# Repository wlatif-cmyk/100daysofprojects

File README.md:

100 Days of Projects — TikTok Series 

https://www.tiktok.com/@yappingaddiction

https://www.instagram.com/yappingaddiction/

Welcome to my 100-day challenge!  

Every day, I build something small, fun, or weird — and post it on TikTok.  

This repo collects the code, notes, and mini-projects from each day.

Follow along as this slowly turns into a chaotic but glorious archive of experiments. 

---

📆 Daily Projects

Day 1 — Traffic light system

Day 2 — Light meter that runs off of ultrasonic sensor

Day 3 — Ball game with LCD Module

Day 4 — Fan Motion Detection 

Day 5 — LED colour changer

Day 6 — Anti-procrastination tool

Day 7 — Anti-procrastination tool major improvements - added timer, timer reset button, and improved screen contrasting

Day 8 — LED Night light

Day 9 — Button piano

Day 10 — Improvements to LED night light - added alarm system

Day 11 — Clothing temperature/humidity sensor

Day 12 — Arduino project generator

Day 13 — Servo motor joystick control

Day 14 — Servo motor joystick control + Remote control using IR sensors

Day 15 — Budgeting dashboard site 

Day 16 — Servo motor hand recognition control

Day 17 — Servo motor hand recognition control2 - same concept but motor moves when hand open/closes

Day 18 — Interview prep tool to prioritize/learn proper eye contact 

Day 19 — Funny face tool using OpenCV

Day 20 — Advanced touchless volume controller

Day 21 — Motion gesture controlled brightness

Day 22 — Motion gesture cursor 

Day 23 — Spotify playlist analyzer

Day 24 — Currency converter 

Day 25 — Weather app

Day 26 — To do list app

Day 27 — "Panda" - designer player upon detection of panda plushie 

Day 28 — Basic chatbot

Day 29 — Number guesser

Day 30 — Motion gesture controlled LED 

Day 31 — RFID card reader 

Day 32 — Password manager 

Day 33 — Expense Tracker

Day 34 — Soldered project (no code)

Day 35 — Cheat code controlled door lock 

Day 36 — Added pin unlock on phone for door lock 

Day 37 — Built final prototype for door lock 

Day 38 — Portable system wiring (No code)

Day 39 — Joystick controlled cursor

Day 40 — Hypnotic art drawing game on python

Day 41 — Esp32 portable communication led project 

Day 42 — Mood bot

Day 43 — Mini Spotify display 

Day 44 — Added buttons to Spotify display 

Day 45 — Math alarm clock 

Day 46 — Improved math alarm clock

Day 47 — STM32 power modes 

Day 48 — Pong on joysticks

Day 49 — ESP32 WIFI network ranking

Day 50 — Balloon popper 

Day 51 — Productivity measure using CV 

Day 52 — ESP32 WIFI channel interference detector 

Day 53 — Improved day 18 project (interview eye contact detector) to give score afterward

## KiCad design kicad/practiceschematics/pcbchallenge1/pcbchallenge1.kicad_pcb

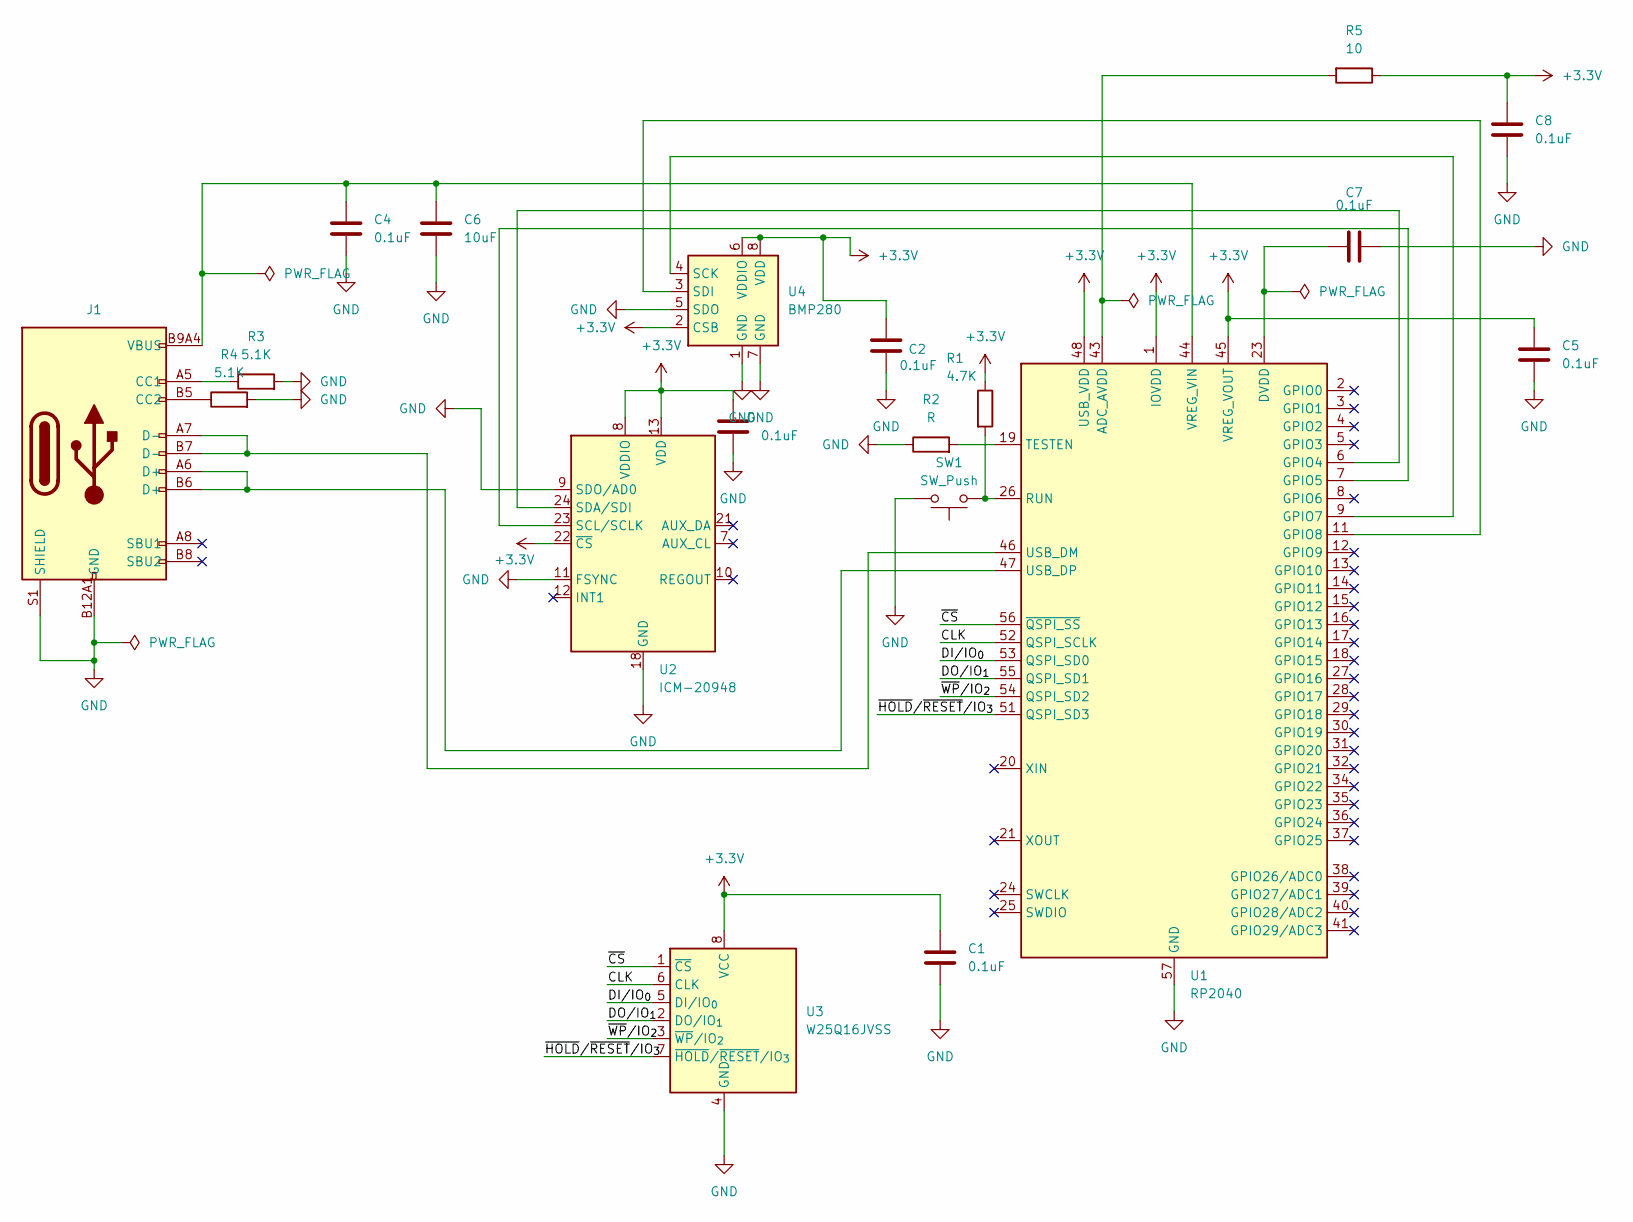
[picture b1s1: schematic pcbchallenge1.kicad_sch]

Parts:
C1, C2, C3, C4, C5, C7, C8: 0.1uF; CP_Elec_3x5.3
C6: 10uF; CP_Elec_4x5.8
J1: Connector, USB-TYPE-C-16P; TYPE-C-SMD_HX-TYPE-C-16PIN; LCSC C2927039
R1: 4.7K; R_0201_0603Metric
R2: R; R_0201_0603Metric
R3, R4: 5.1K; R_0201_0603Metric
R5: 10; R_0201_0603Metric
SW1: SW_Push; R_0201_0603Metric
U1: RP2040; QFN-56-1EP_7x7mm_P0.4mm_EP3.2x3.2mm
U2: ICM-20948; InvenSense_QFN-24_3x3mm_P0.4mm
U3: W25Q16JVSS; SOIC-8_5.3x5.3mm_P1.27mm
U4: BMP280; Bosch_LGA-8_2x2.5mm_P0.65mm_ClockwisePinNumbering

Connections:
+3.3V: C1.1, C2.1, C3.1, C5.1, C8.1, R1.1, R5.1, U1.1 (IOVDD), U1.10 (IOVDD), U1.22 (IOVDD), U1.33 (IOVDD), U1.42 (IOVDD), U1.45 (VREG_VOUT), U1.48 (USB_VDD), U1.49 (IOVDD), U2.8 (VDDIO), U2.13 (VDD), U2.22 (~CS), U3.8 (VCC), U4.2 (CSB), U4.6 (VDDIO), U4.8 (VDD)
GND: C1.2, C2.2, C3.2, C4.2, C5.2, C6.2, C7.2, C8.2, J1.A12B1 (GND), J1.B12A1 (GND), J1.S1 (SHIELD), R2.1, R3.2, R4.2, SW1.2, U1.57 (GND), U2.9 (SDO/AD0), U2.11 (FSYNC), U2.18 (GND), U2.20 (GND), U3.4 (GND), U4.1 (GND), U4.5 (SDO), U4.7 (GND)
unnamed: C7.1, U1.23 (DVDD), U1.50 (DVDD)
unnamed: J1.A5 (CC1), R3.1
unnamed: J1.B5 (CC2), R4.1
unnamed: R5.2, U1.43 (ADC_AVDD)
unnamed: U1.6 (GPIO4), U2.24 (SDA/SDI)
unnamed: U1.7 (GPIO5), U2.23 (SCL/SCLK)
unnamed: U1.9 (GPIO7), U4.4 (SCK)
unnamed: U1.11 (GPIO8), U4.3 (SDI)
unnamed: U1.52 (QSPI_SCLK), U3.6 (CLK)
unnamed: U1.53 (QSPI_SD0), U3.5 (DI/IO_{0})
unnamed: U1.55 (QSPI_SD1), U3.2 (DO/IO_{1})
unnamed: U1.54 (QSPI_SD2), U3.3 (~WP/IO_{2})
unnamed: U1.51 (QSPI_SD3), U3.7 (~HOLD/~RESET/IO_{3})
unnamed: R1.2, SW1.1, U1.26 (RUN)
unnamed: R2.2, U1.19 (TESTEN)
unnamed: J1.A7 (D-), J1.B7 (D-), U1.46 (USB_DM)
unnamed: J1.A6 (D+), J1.B6 (D+), U1.47 (USB_DP)
unnamed: C4.1, C6.1, J1.A9B4 (VBUS), J1.B9A4 (VBUS), U1.44 (VREG_VIN)
unnamed: U1.56 (~QSPI_SS), U3.1 (~CS)

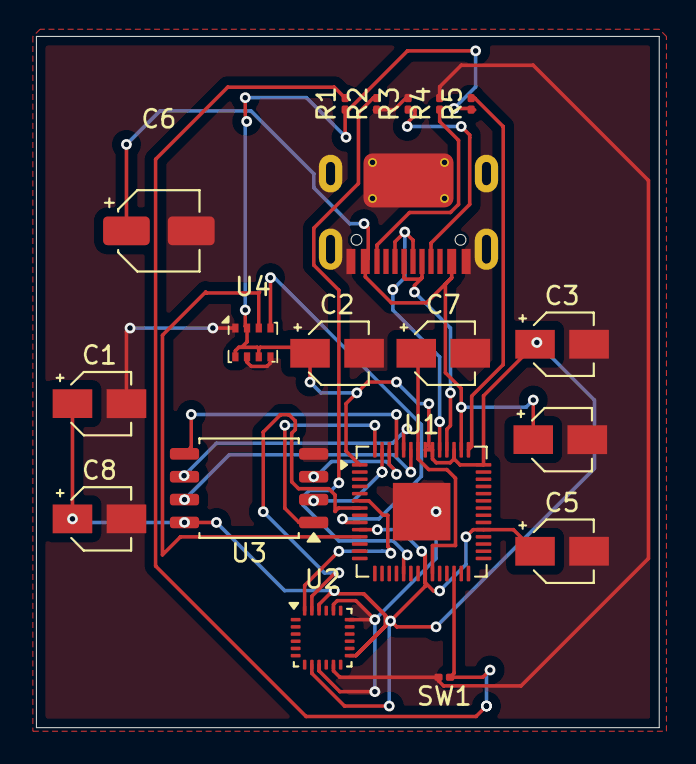
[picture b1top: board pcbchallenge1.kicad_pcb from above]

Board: 2 copper layers, 34.6 x 38.4 mm, 19 parts (0 on the bottom side), 21 nets.

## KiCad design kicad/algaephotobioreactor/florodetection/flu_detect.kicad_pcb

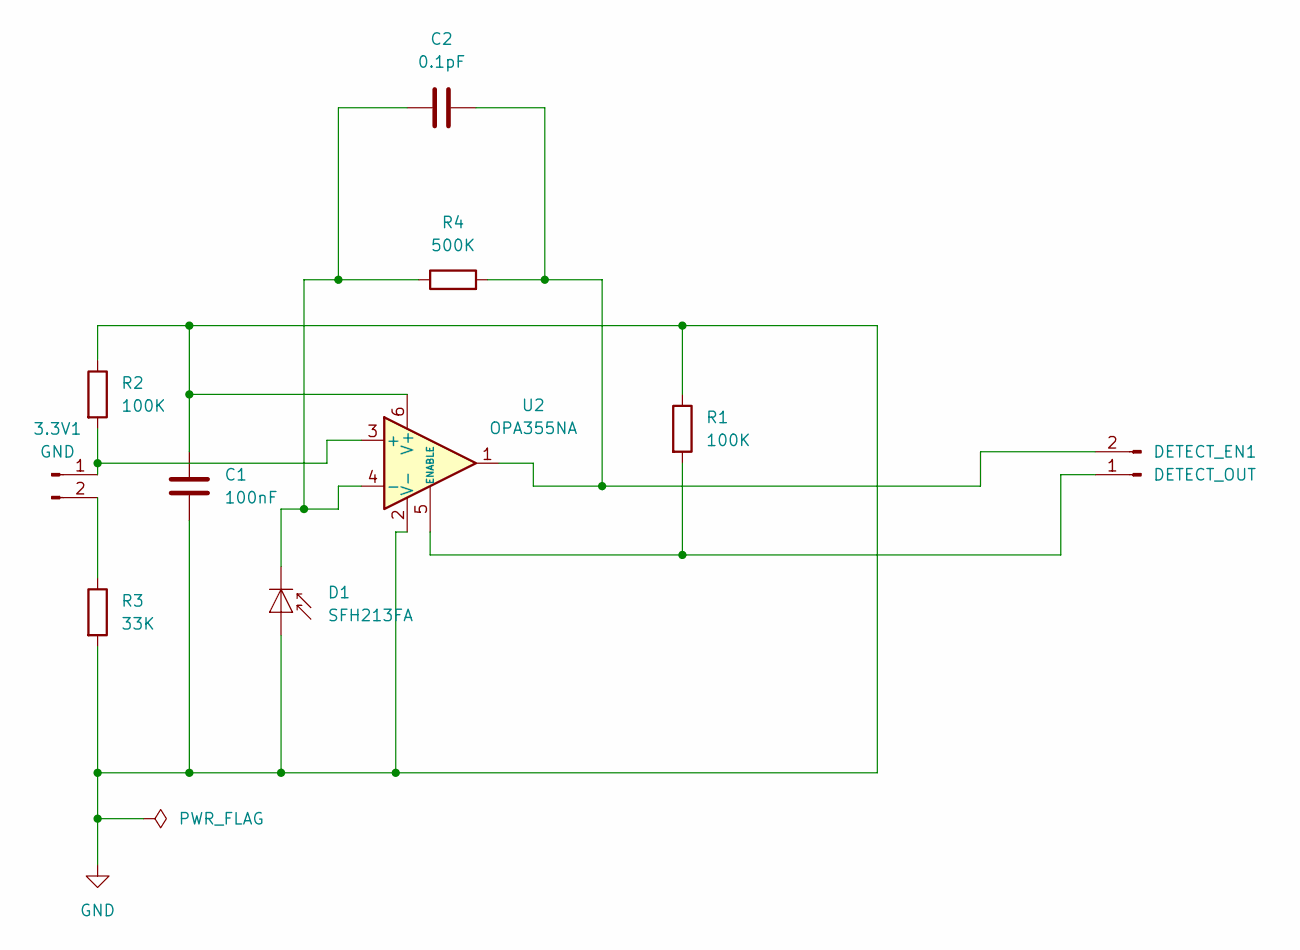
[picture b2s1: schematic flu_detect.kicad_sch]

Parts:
3.3V1: GND; PinHeader_1x04_P2.54mm_Vertical
C1: 100nF; CP_Elec_3x5.3
C2: 0.1pF; CP_Elec_3x5.3
D1: SFH213FA; LED_D5.0mm_IRGrey
DETECT_EN1: DETECT_OUT; TerminalBlock_Phoenix_PTSM-0,5-2-2,5-V-SMD_1x02-1MP_P2.50mm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
R1, R2: 100K; R_0201_0603Metric
R3: 33K; R_0201_0603Metric
R4: 500K; R_0201_0603Metric
U2: OPA355NA; SOT-23-6

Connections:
GND: C1.1, C1.2, D1.2 (A), R1.1, R2.1, R3.2, U2.2 (V-), U2.6 (V+)
unnamed: 3.3V1.1, R2.2, U2.3 (+)
unnamed: 3.3V1.2, R3.1
unnamed: C2.1, D1.1 (K), R4.1, U2.4 (-)
unnamed: DETECT_EN1.1, R1.2, U2.5 (ENABLE)
unnamed: C2.2, DETECT_EN1.2, R4.2, U2.1

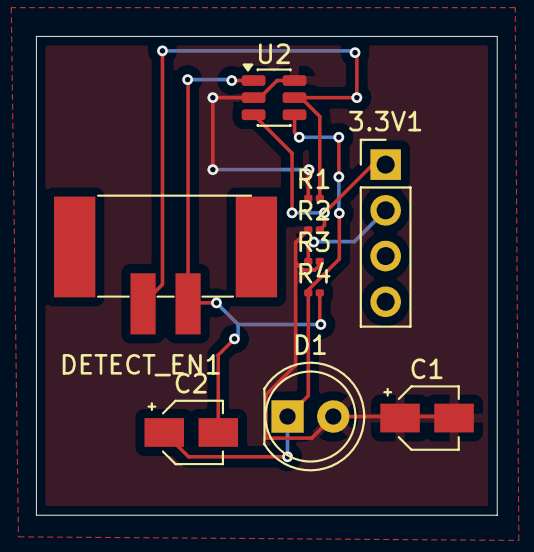
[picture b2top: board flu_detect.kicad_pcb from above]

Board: 2 copper layers, 25.6 x 26.6 mm, 10 parts (0 on the bottom side), 6 nets.

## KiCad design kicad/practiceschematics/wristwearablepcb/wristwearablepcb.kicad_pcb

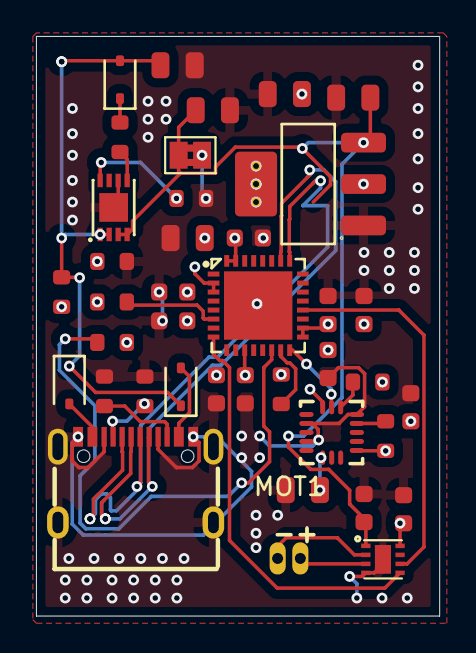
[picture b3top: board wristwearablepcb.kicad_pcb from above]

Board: 4 copper layers, 22.4 x 32.2 mm, 39 parts (0 on the bottom side), 23 nets.

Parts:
BT1: Battery; SolderJumper-2_P1.3mm_Bridged2Bar_Pad1.0x1.5mm
C1, C11, C12: 10uF; C_0805
C2: 22uF; C_0805
C3, C8, C9, C13: 100nF; C_0603
C4, C5, C6, C10: 1uF; C_0603
C7: 10nF; C_0603
C14, C15: 4.7uF; C_0805
C16, C17: 0.1uF; C_0603
D1, D2, D3: 1N5819WS; D_SOD-323
MOT1: LCM1027A2445F; VIBRATING-MOTOR-SMD_WELDING
R1, R2: 5.1k; R_0603
R3: 18kΩ; R_0603
R4: 33kΩ; R_0603
R7, R8, R11: 10k; R_0603
R9: 2k; R_0603
R10: 470; R_0603
R_SCL1: 10k; R_0603
R_SDA1: 10k; R_0603
U1: AMS1117; SOT-223-3_L6.5-W3.4-P2.30-LS7.0-BR
U2: LIS3DHTR_C15134; LGA-16_L3.0-W3.0-P0.50-TL
U3: ESP32-C3; QFN-32_L5.0-W5.0-P0.50-TL-EP3.7
U4: MCP73831-2ACI/MC; TDFN-8_L3.0-W2.0-P0.50-BL-EP1.6
U5: DRV8837DSGR; WSON-8_L2.0-W2.0-P0.50-TL-EP
USB1: TYPE-C 16PIN 2MD(073); USB-C-SMD_TYPE-C-6PIN-2MD-073

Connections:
+3.3V: C2.1, C3.1, C4.1, C5.1, C6.1, C7.1, C8.1, C9.1, C10.1, C11.1, C12.2, C13.2, C17.1, R3.2, R4.1, R7.1, R8.2, R11.2, R_SCL1.1, R_SDA1.1, U1.2 (VOUT), U1.4 (VOUT), U2.1 (VDD_IO), U2.8 (CS), U2.14 (VDD), U3.2 (VDD3P3), U3.3 (VDD3P3), U3.11 (VDD3P3_RTC), U3.17 (VDD3P3_CPU), U3.18 (VDD_SPI), U3.31 (VDDA), U3.32 (VDDA), U5.8 (VCC)
+5V: C14.1, D1.1, D2.1, D3.2, R3.1, U4.1 (VDD), U4.2 (VDD)
/3.7V LiPo: BT1.1 (+), C1.1, C15.1, C16.1, U1.3 (VIN), U4.3 (VBAT), U4.4 (VBAT), U5.1 (VM)
/D+: U3.26 (GPIO19), USB1.6 (DP1), USB1.8 (DP2)
/D-: U3.25 (GPIO18), USB1.5 (DN2), USB1.7 (DN1)
/IN1: U3.20 (SPIWP), U5.6 (IN1)
/IN2: U3.8 (GPIO3), U5.5 (IN2)
/SCL: R_SCL1.2, U2.4 (SCL/SPC)
/SDA: R_SDA1.2, U2.6 (SDA/SDI/SDO)
/SDO: U2.7 (SDO/SA0), U3.16 (GPIO10)
GND: BT1.2 (-), C1.2, C2.2, C3.2, C4.2, C5.2, C6.2, C7.2, C8.2, C9.2, C10.2, C11.2, C12.1, C13.1, C14.2, C15.2, C16.2, C17.2, R1.1, R2.1, R4.2, R9.2, U1.1 (GND), U2.5 (GND), U2.10 (RES), U2.12 (GND), U3.33 (EP), U4.6 (VSS), U4.9 (EP), U5.4 (GND), U5.9 (EP), USB1.1 (GND), USB1.3 (SBU2), USB1.9 (SBU1), USB1.12 (GND), USB1.13 (SHELL), USB1.14 (SHELL)
unnamed: D1.2, USB1.2 (VBUS)
unnamed: D2.2, USB1.11 (VBUS)
unnamed: D3.1, R10.1
unnamed: MOT1.2 (+), U5.3 (OUT2)
unnamed: MOT1.1 (-), U5.2 (OUT1)
unnamed: R7.2, U3.6 (GPIO2)
unnamed: R8.1, U3.14 (GPIO8)
unnamed: R11.1, U3.15 (GPIO9)
unnamed: R9.1, U4.8 (PROG)
unnamed: R10.2, U4.5 (STAT)
unnamed: R1.2, USB1.4 (CC1)
unnamed: R2.2, USB1.10 (CC2)

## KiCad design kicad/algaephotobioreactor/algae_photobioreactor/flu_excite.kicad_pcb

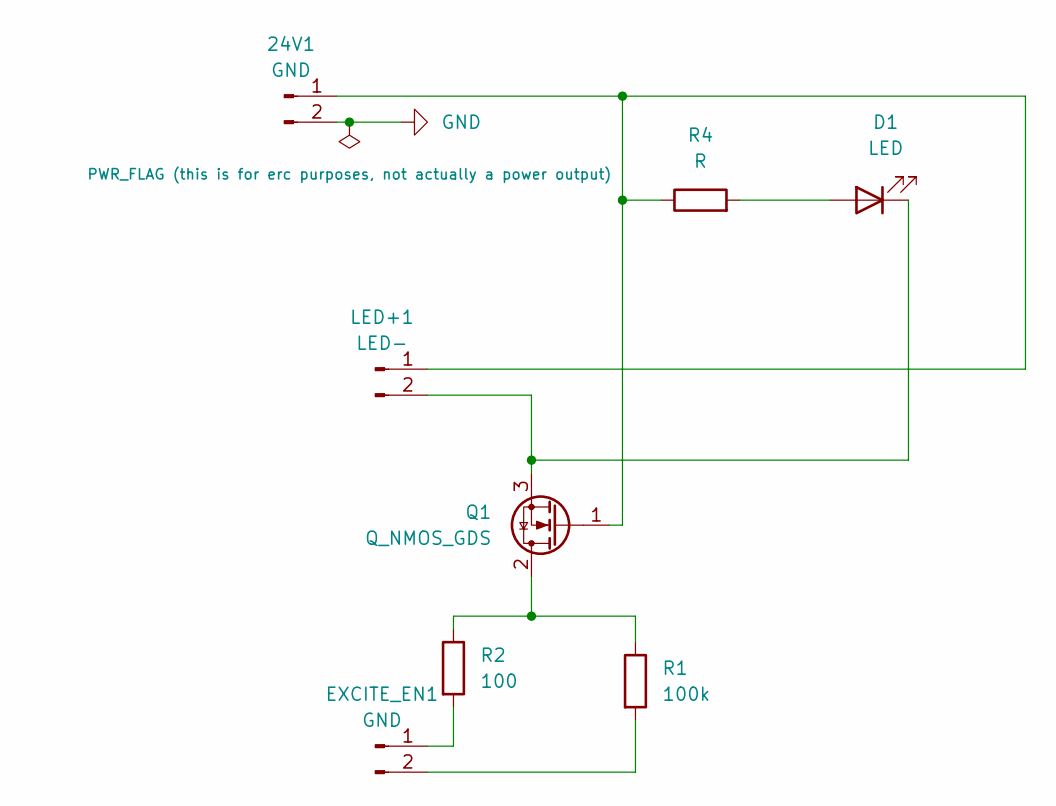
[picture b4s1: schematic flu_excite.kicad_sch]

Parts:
24V1: GND; TerminalBlock_Phoenix_MKDS-1,5-2-5.08_1x02_P5.08mm_Horizont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
D1: LED; TerminalBlock_Phoenix_MKDS-1,5-2-5.08_1x02_P5.08mm_Horizont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
EXCITE_EN1: GND; PinHeader_1x02_P2.54mm_Vertical
LED+1: LED-; LED_D3.0mm
Q1: Q_NMOS_GDS; SOT-23
R1: 100k; R_1206_3216Metric
R2: 100; R_1206_3216Metric
R4: R; R_1206_3216Metric

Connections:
GND: 24V1.2
unnamed: 24V1.1, LED+1.1, Q1.1 (G), R4.1
unnamed: D1.2 (A), R4.2
unnamed: D1.1 (K), LED+1.2, Q1.3 (S)
unnamed: EXCITE_EN1.1, R2.2
unnamed: EXCITE_EN1.2, R1.2
unnamed: Q1.2 (D), R1.1, R2.1

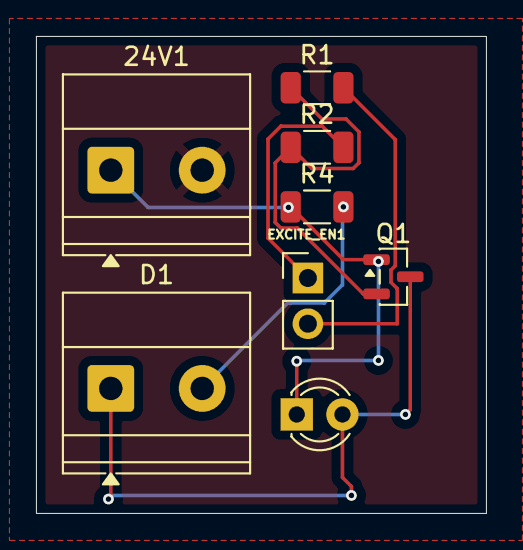
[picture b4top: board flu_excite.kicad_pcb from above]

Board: 2 copper layers, 25.0 x 26.5 mm, 8 parts (0 on the bottom side), 6 nets.

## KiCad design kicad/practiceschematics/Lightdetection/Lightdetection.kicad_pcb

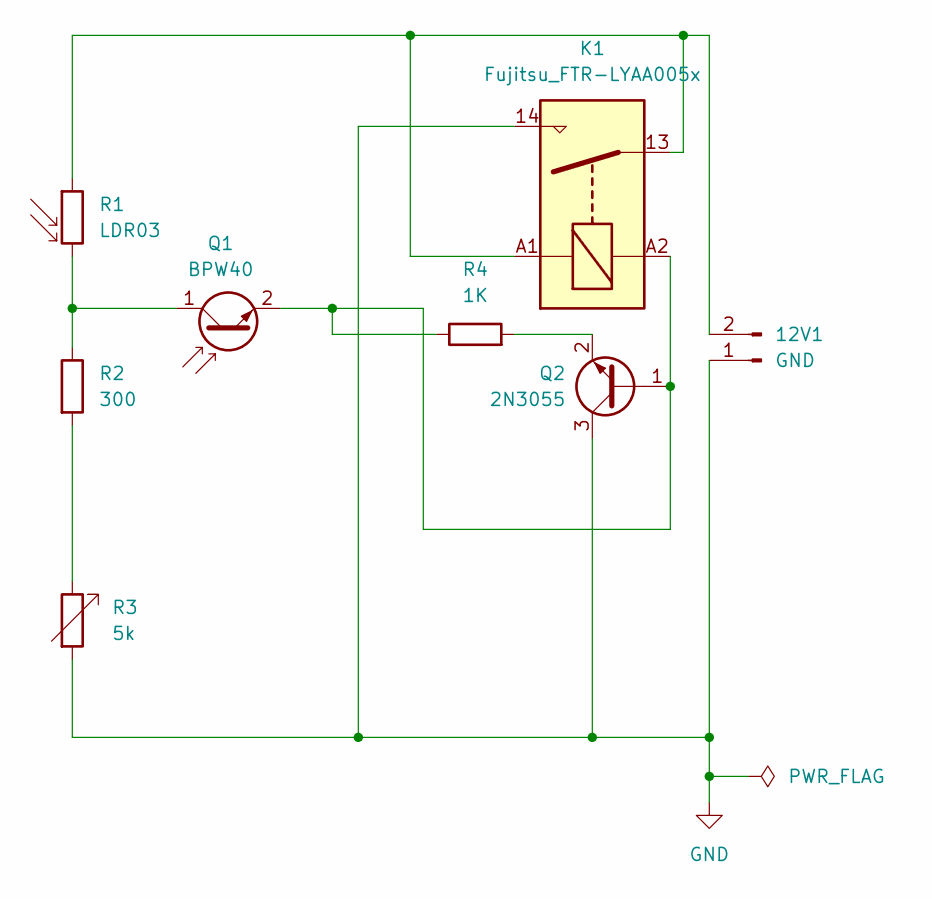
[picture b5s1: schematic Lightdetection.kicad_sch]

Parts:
12V1: GND; BatteryHolder_TruPower_BH-331P_3xAA
K1: Fujitsu_FTR-LYAA005x; Relay_SPST-NO_Fujitsu_FTR-LYAA005x_FormA_Vertical
Q1: BPW40; LED_D5.0mm_Clear
Q2: 2N3055; TO-3
R1: LDR03; R_LDR_10x8.5mm_P7.6mm_Vertical
R2: 300; R_0201_0603Metric
R3: 5k; R_0201_0603Metric
R4: 1K; R_0201_0603Metric

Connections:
GND: 12V1.1, K1.14, Q2.3 (C), R3.2
unnamed: 12V1.2, K1.13, K1.A1, R1.1
unnamed: Q1.1 (C), R1.2, R2.1
unnamed: K1.A2, Q1.2 (E), Q2.1 (B), R4.1
unnamed: Q2.2 (E), R4.2
unnamed: R2.2, R3.1

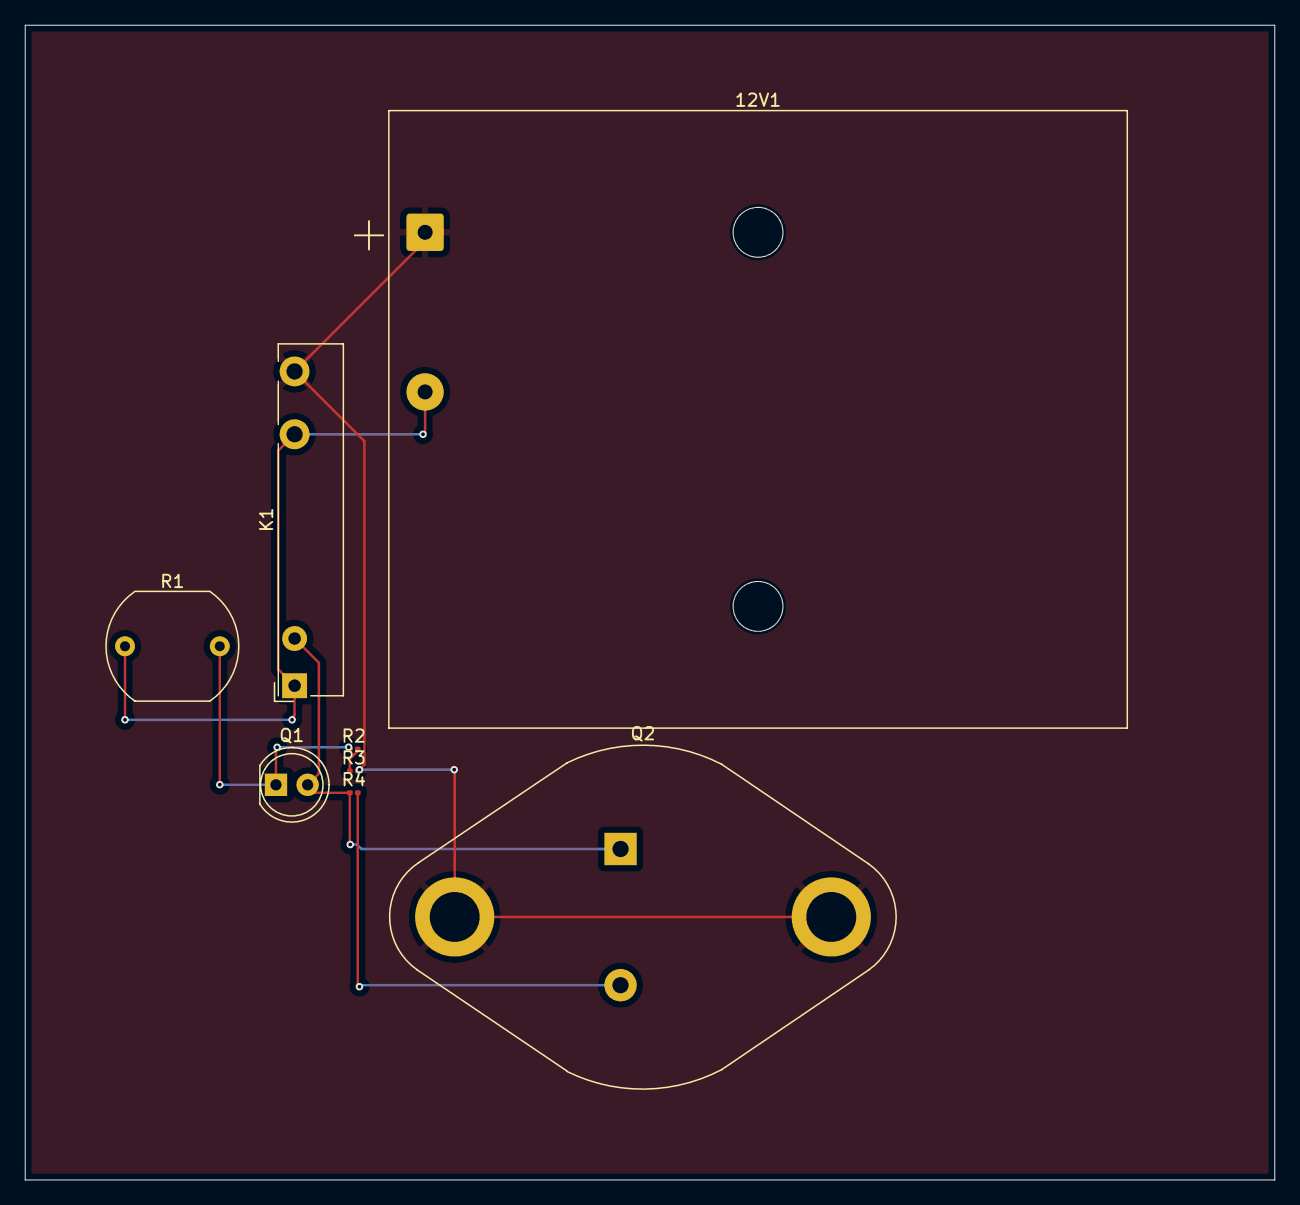
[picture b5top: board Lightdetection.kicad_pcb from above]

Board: 2 copper layers, 100.2 x 92.6 mm, 8 parts (0 on the bottom side), 6 nets.

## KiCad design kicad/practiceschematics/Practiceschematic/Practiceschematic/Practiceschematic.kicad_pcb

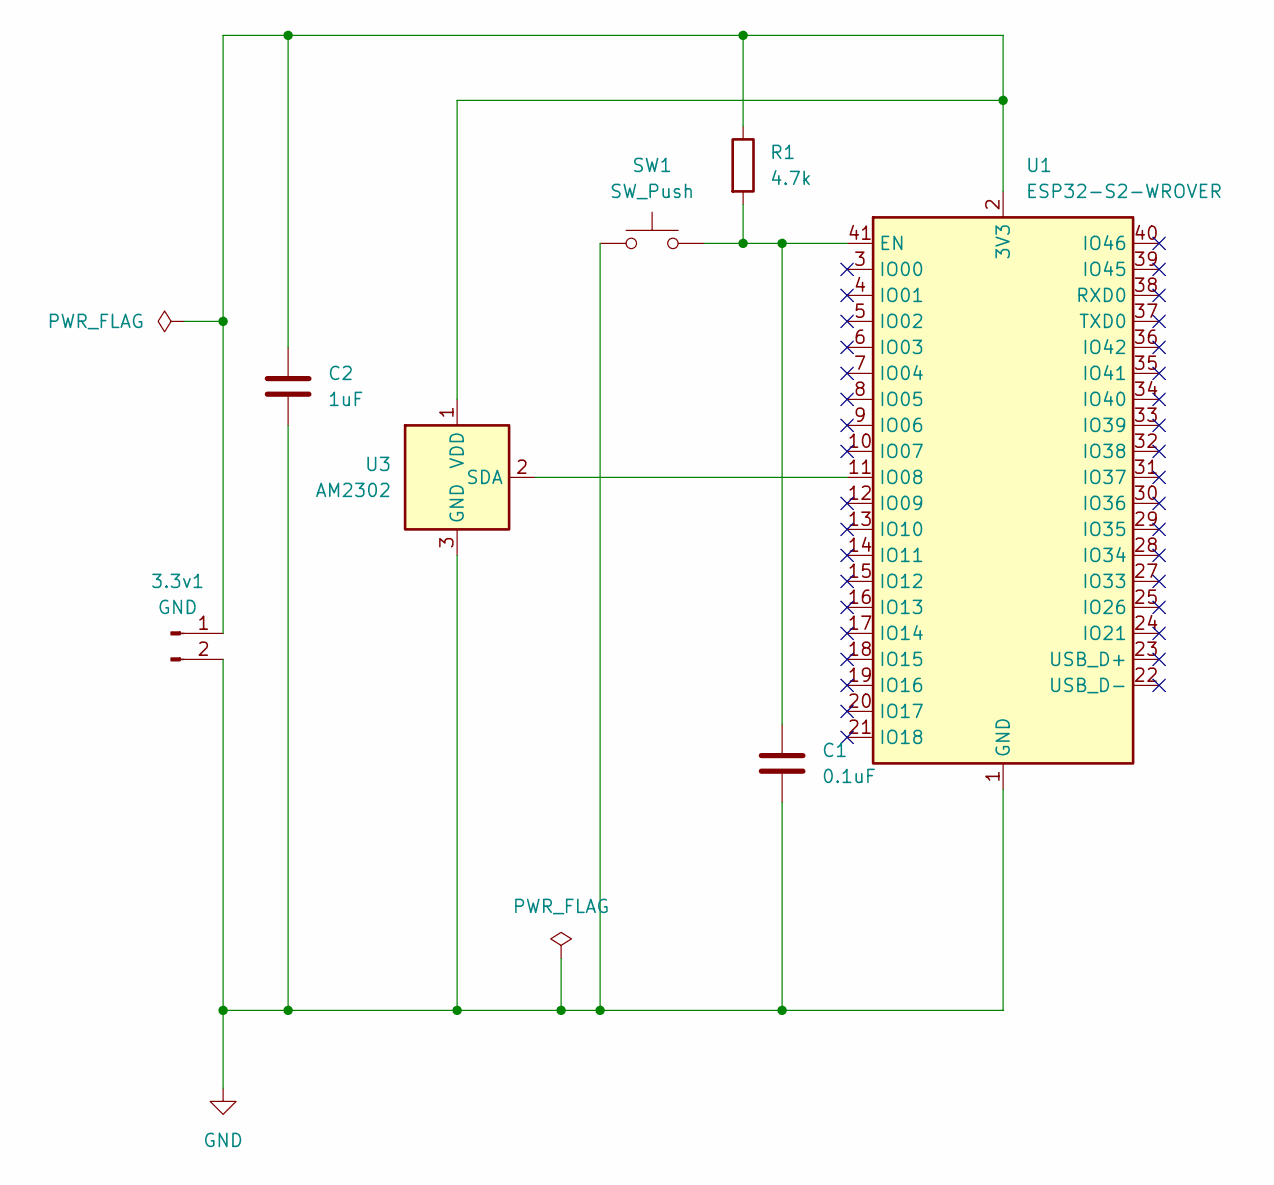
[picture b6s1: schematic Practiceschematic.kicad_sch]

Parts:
3.3v1: GND; BatteryHolder_TruPower_BH-331P_3xAA
C1: 0.1uF; CP_Elec_3x5.3
C2: 1uF; CP_Elec_3x5.3
R1: 4.7k; R_0201_0603Metric
SW1: SW_Push; SW_Cherry_MX_1.00u_PCB
U1: ESP32-S2-WROVER
U3: AM2302; ASAIR_AM2302_P2.54mm_Vertical

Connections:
GND: 3.3v1.2, C1.2, C2.2, SW1.1, U1.1 (GND), U1.26 (GND), U1.42 (GND), U1.43 (GND), U3.3 (GND), U3.4 (GND)
unnamed: 3.3v1.1, C2.1, R1.1, U1.2 (3V3), U3.1 (VDD)
unnamed: C1.1, R1.2, SW1.2, U1.41 (EN)
unnamed: U1.11 (IO08), U3.2 (SDA)

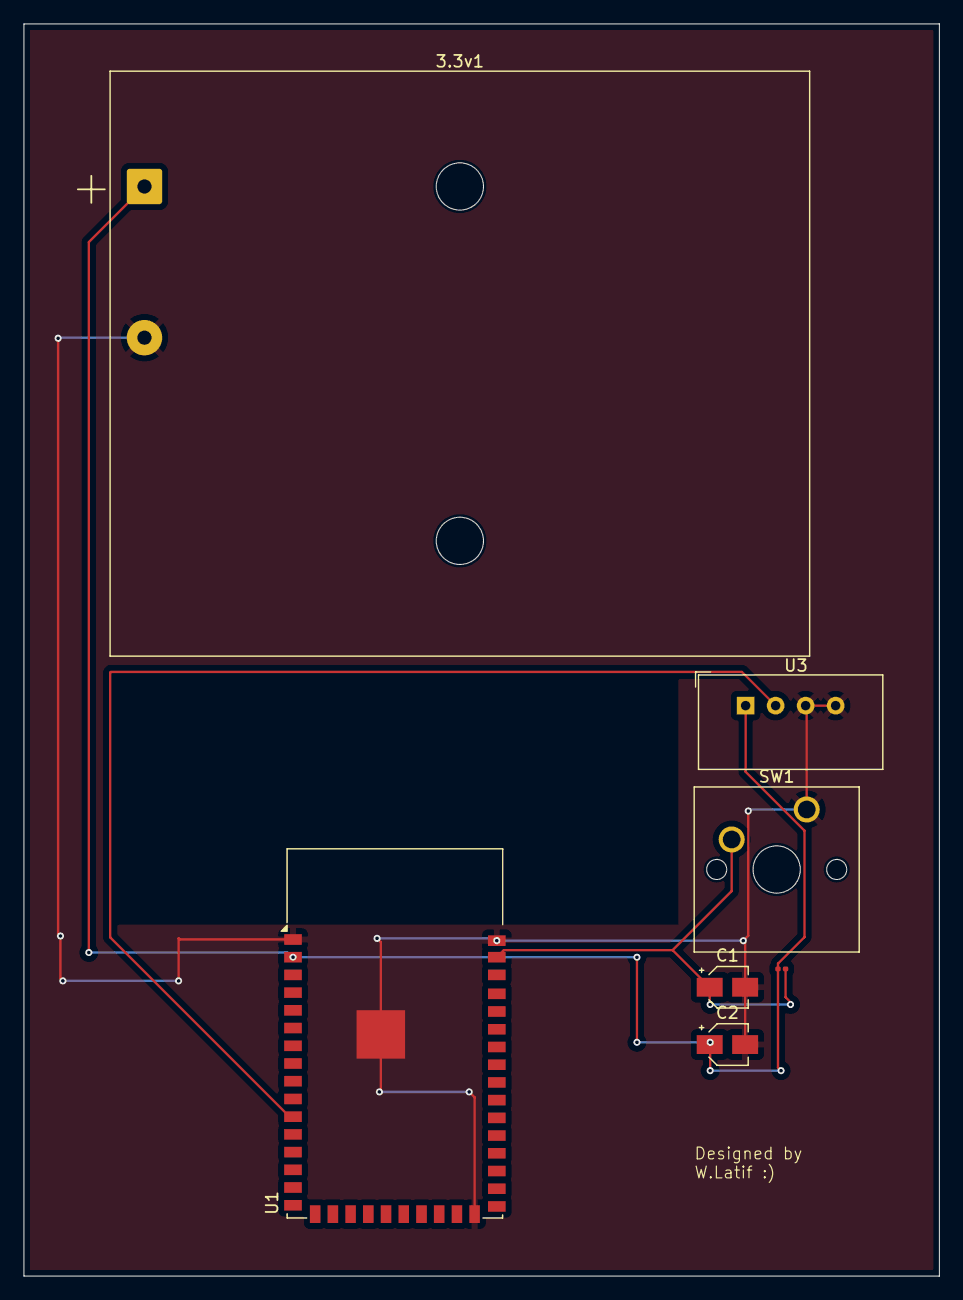
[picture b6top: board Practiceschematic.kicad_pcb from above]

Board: 2 copper layers, 77.5 x 106.0 mm, 7 parts (0 on the bottom side), 4 nets.

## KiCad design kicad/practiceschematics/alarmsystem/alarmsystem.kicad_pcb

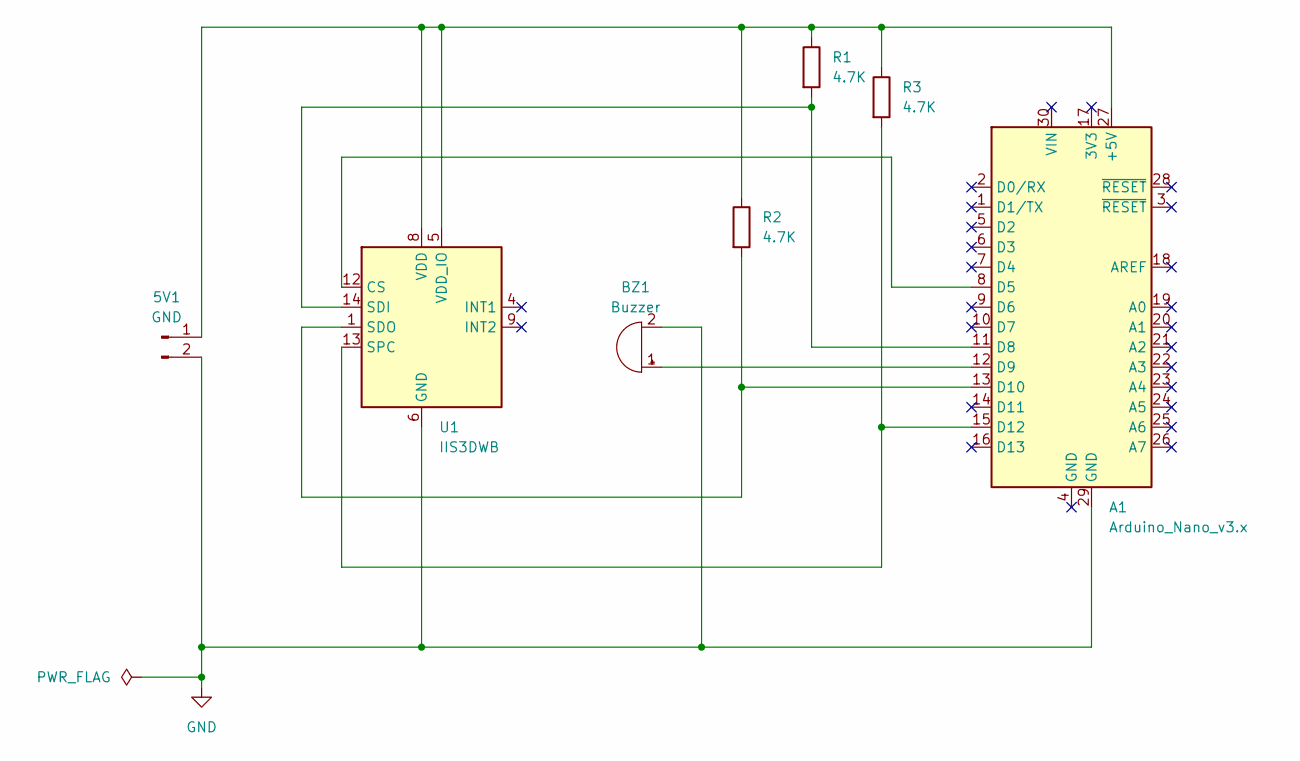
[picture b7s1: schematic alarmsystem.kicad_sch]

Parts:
5V1: GND; BatteryHolder_TruPower_BH-331P_3xAA
A1: Arduino_Nano_v3.x; Arduino_Nano
BZ1: Buzzer; Buzzer_12x9.5RM7.6
R1, R2, R3: 4.7K; R_0201_0603Metric
U1: IIS3DWB; LGA-14_3x2.5mm_P0.5mm_LayoutBorder3x4y; MPN IIS3DWBTR

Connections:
GND: 5V1.2, A1.29 (GND), BZ1.2 (-), U1.2 (GND), U1.3 (GND), U1.6 (GND), U1.7 (GND)
unnamed: 5V1.1, A1.27 (+5V), R1.1, R2.1, R3.1, U1.5 (VDD_IO), U1.8 (VDD)
unnamed: A1.8 (D5), U1.12 (CS)
unnamed: A1.11 (D8), R1.2, U1.14 (SDI)
unnamed: A1.12 (D9), BZ1.1 (+)
unnamed: A1.13 (D10), R2.2, U1.1 (SDO)
unnamed: A1.15 (D12), R3.2, U1.13 (SPC)

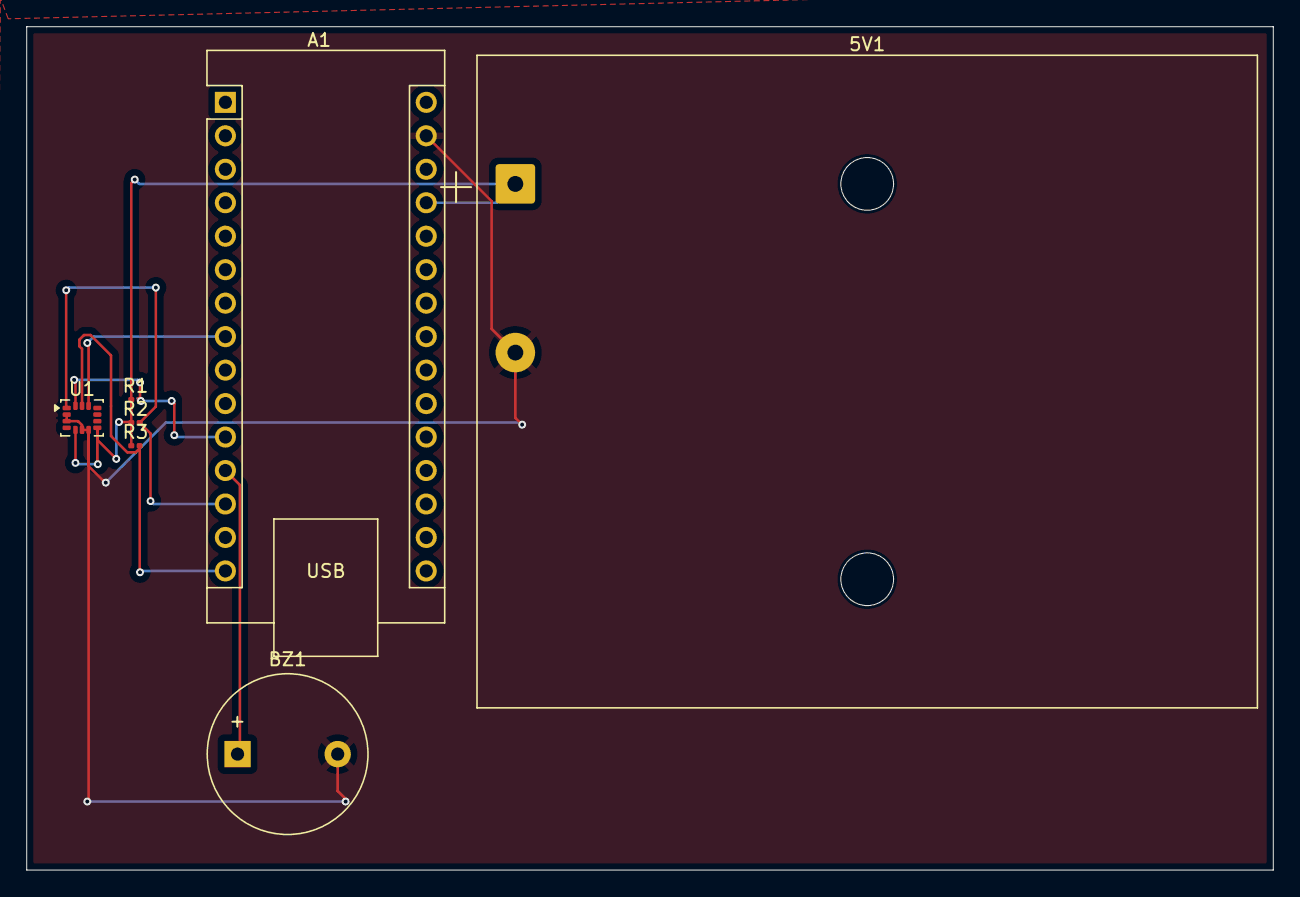
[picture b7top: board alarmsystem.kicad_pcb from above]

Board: 2 copper layers, 94.6 x 64.0 mm, 7 parts (0 on the bottom side), 7 nets.

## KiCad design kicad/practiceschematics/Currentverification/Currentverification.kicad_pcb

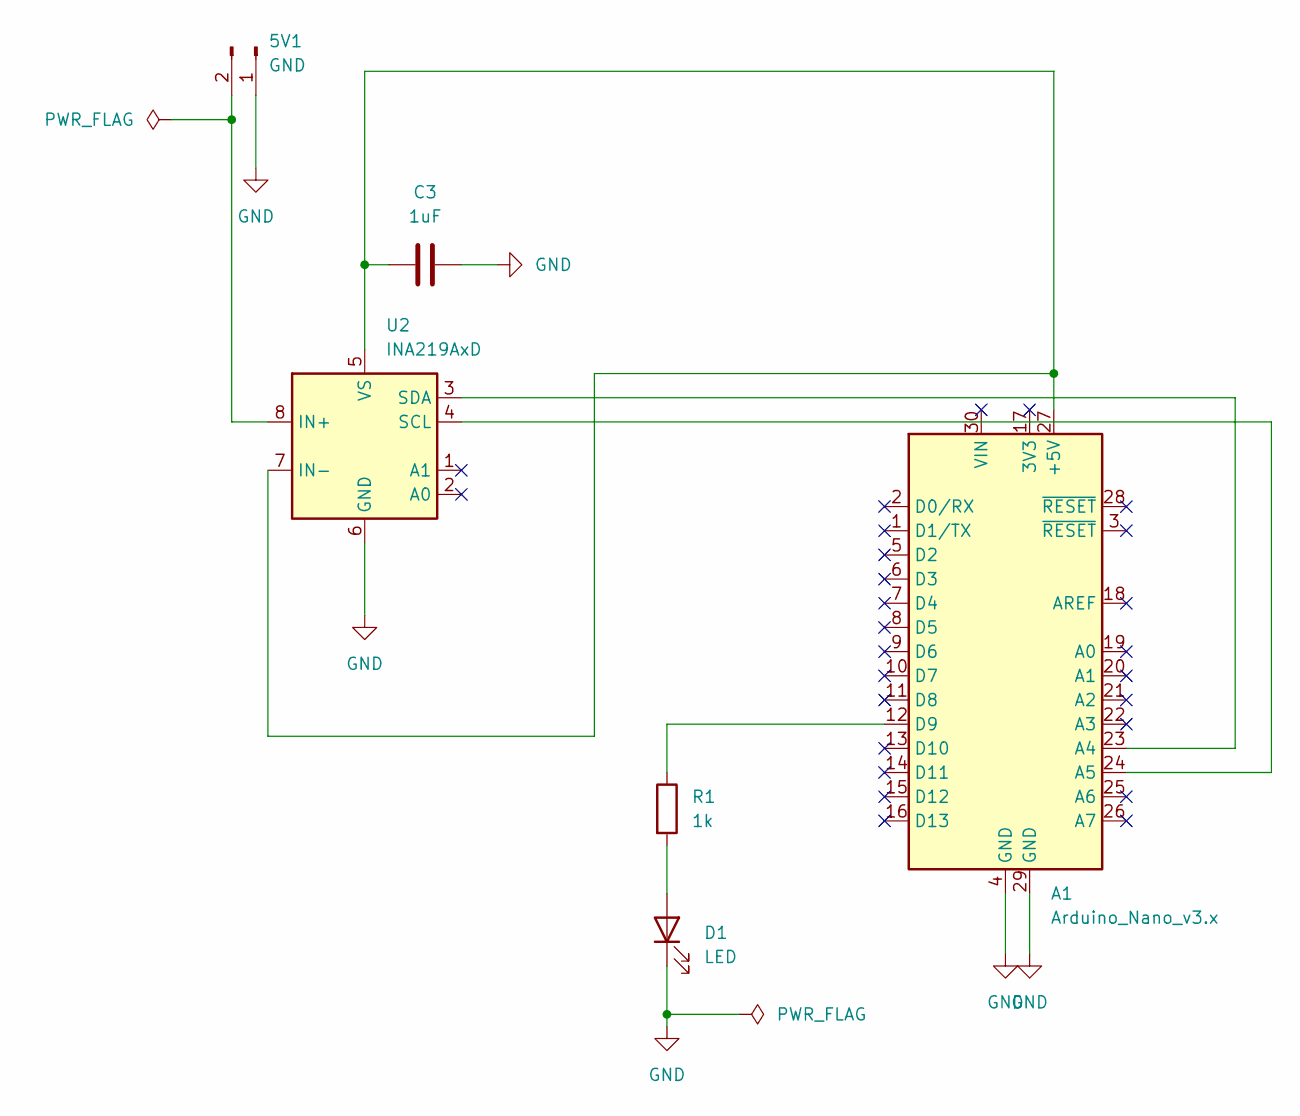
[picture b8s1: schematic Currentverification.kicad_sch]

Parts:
5V1: GND; PinHeader_1x02_P2.54mm_Vertical
A1: Arduino_Nano_v3.x; Arduino_Nano
C3: 1uF; C_0805_2012Metric
D1: LED; LED_D5.0mm
R1: 1k; R_Axial_DIN0204_L3.6mm_D1.6mm_P1.90mm_Vertical
U2: INA219AxD; SOIC-8_3.9x4.9mm_P1.27mm

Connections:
GND: 5V1.1, A1.4 (GND), A1.29 (GND), C3.2, D1.1 (K), U2.6 (GND)
unnamed: 5V1.2, U2.8 (IN+)
unnamed: A1.27 (+5V), C3.1, U2.5 (VS), U2.7 (IN-)
unnamed: A1.23 (A4), U2.3 (SDA)
unnamed: A1.24 (A5), U2.4 (SCL)
unnamed: A1.12 (D9), R1.1
unnamed: D1.2 (A), R1.2

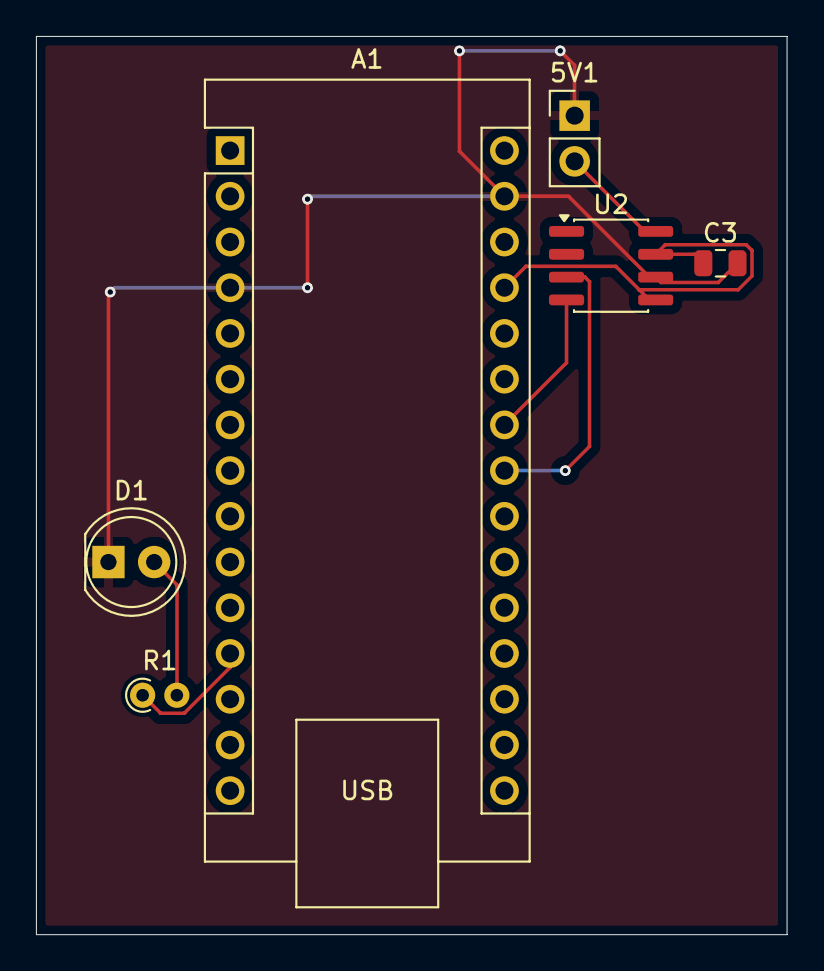
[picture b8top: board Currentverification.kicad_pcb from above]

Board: 2 copper layers, 41.7 x 49.9 mm, 6 parts (0 on the bottom side), 7 nets.

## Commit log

2025-11-15 added fan motion detection code
2025-11-16 updated d5 read me
2025-11-17 updated read me for day 6 and added anti procrastination tool
2025-11-18 updated for day 7, improved anti procrast. tool
2025-11-19 added led night light
2025-11-21 added day 10, 11 and updated readme to match repo
2025-11-24 updated read me dates and added servo motor control project
2025-11-24 UI: Remove all boxes from project card and title, keep everything transparent and clean
2025-11-24 dlsfms
2025-11-26 added budgeting dashboard html
2025-11-27 updated read me, added hand recog. servo project
2025-11-29 hand recog changes
2025-11-29 added eye contact detection/interview prep project
2025-12-02 added day 20 & 21
2025-12-04 added spotify playlist analyzer
2025-12-06 added currencyconverter
2025-12-08 make me a calculator and explain it
2025-12-08 added todolist
2025-12-08 added pandaanalyzer with opencv
2025-12-17 added a bunch of projects lol
2025-12-29 added loads of projects from the pas
2026-01-05 added projects
2026-01-05 updated read me from day 18 to day 53
2026-01-07 coderoast
2026-01-15 added few projects
2026-01-30 added kicad projects asw as nba live data project
2026-01-30 removed a few buggy files
2026-02-02 added fluorescence excitement pcb
2026-02-11 added many projects haha
